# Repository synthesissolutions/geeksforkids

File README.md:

# geeksforkids
car_firmware - Code for RC/Joytick controlled cars

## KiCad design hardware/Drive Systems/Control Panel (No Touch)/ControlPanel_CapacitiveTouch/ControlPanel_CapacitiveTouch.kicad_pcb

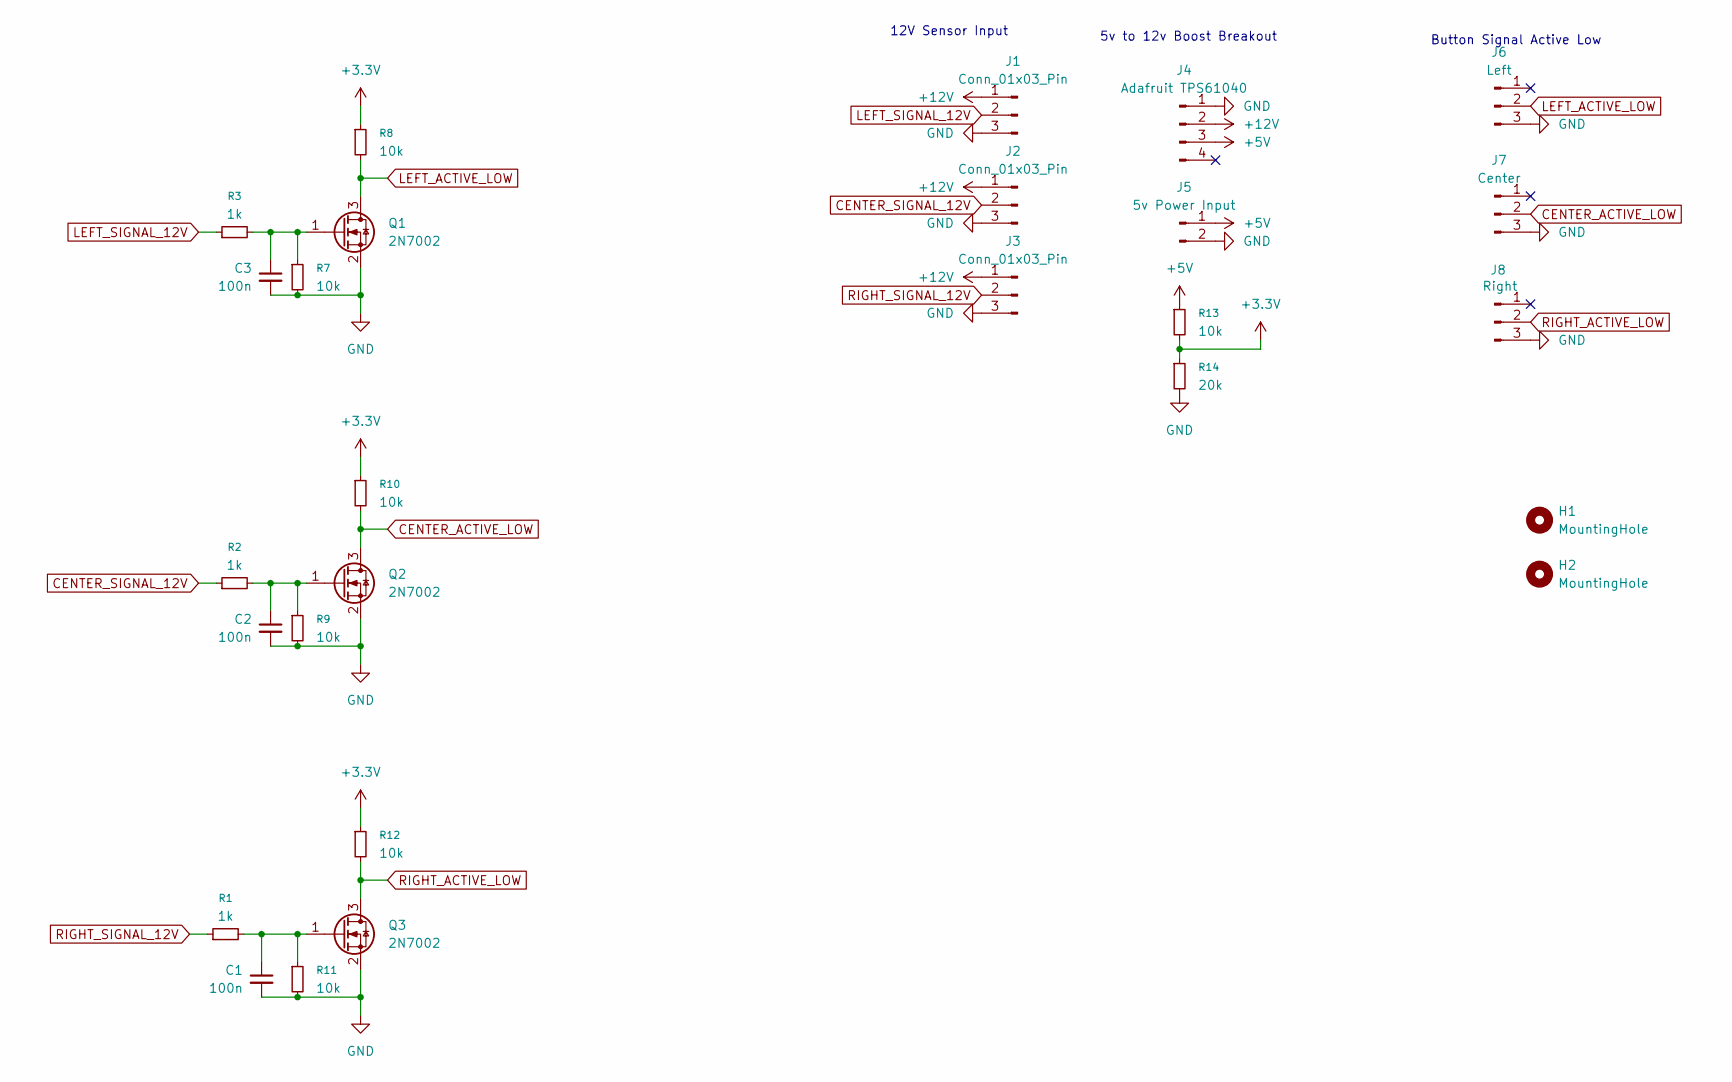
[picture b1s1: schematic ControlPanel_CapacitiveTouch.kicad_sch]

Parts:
C1, C2, C3: 100n; C_0402_1005Metric; MPN C1525
H1, H2: MountingHole; MountingHole_2.7mm_M2.5
J1, J2, J3: Conn_01x03_Pin; JST_PH_B3B-PH-K_1x03_P2.00mm_Vertical
J4: Adafruit TPS61040; PinHeader_1x04_P2.54mm_Vertical
J5: 5v Power Input; JST_XH_B2B-XH-A_1x02_P2.50mm_Vertical
J6: Left; JST_SH_BM03B-SRSS-TB_1x03-1MP_P1.00mm_Vertical; MPN C160403
J7: Center; JST_SH_BM03B-SRSS-TB_1x03-1MP_P1.00mm_Vertical; MPN C160403
J8: Right; JST_SH_BM03B-SRSS-TB_1x03-1MP_P1.00mm_Vertical; MPN C160403
Q1, Q2, Q3: 2N7002; SOT-23; MPN C8545
R1, R2, R3: 1k; R_0402_1005Metric; MPN C11702
R7, R8, R9, R10, R11, R12, R13: 10k; R_0402_1005Metric; MPN C25744
R14: 20k; R_0402_1005Metric; MPN C25765

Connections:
+3.3V: R8.1, R10.1, R12.1, R13.2, R14.1
+5V: J4.3, J5.1, R13.1
+12V: J1.1, J2.1, J3.1, J4.2
CENTER_ACTIVE_LOW: J7.2, Q2.3 (D), R10.2
CENTER_SIGNAL_12V: J2.2, R2.1
GND: C1.2, C2.2, C3.2, J1.3, J2.3, J3.3, J4.1, J5.2, J6.3, J7.3, J8.3, Q1.2 (S), Q2.2 (S), Q3.2 (S), R7.2, R9.2, R11.2, R14.2
LEFT_ACTIVE_LOW: J6.2, Q1.3 (D), R8.2
LEFT_SIGNAL_12V: J1.2, R3.1
unnamed: C3.1, Q1.1 (G), R3.2, R7.1
unnamed: C2.1, Q2.1 (G), R2.2, R9.1
unnamed: C1.1, Q3.1 (G), R1.2, R11.1
RIGHT_ACTIVE_LOW: J8.2, Q3.3 (D), R12.2
RIGHT_SIGNAL_12V: J3.2, R1.1

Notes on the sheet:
5v to 12v Boost Breakout
12V Sensor Input
Button Signal Active Low

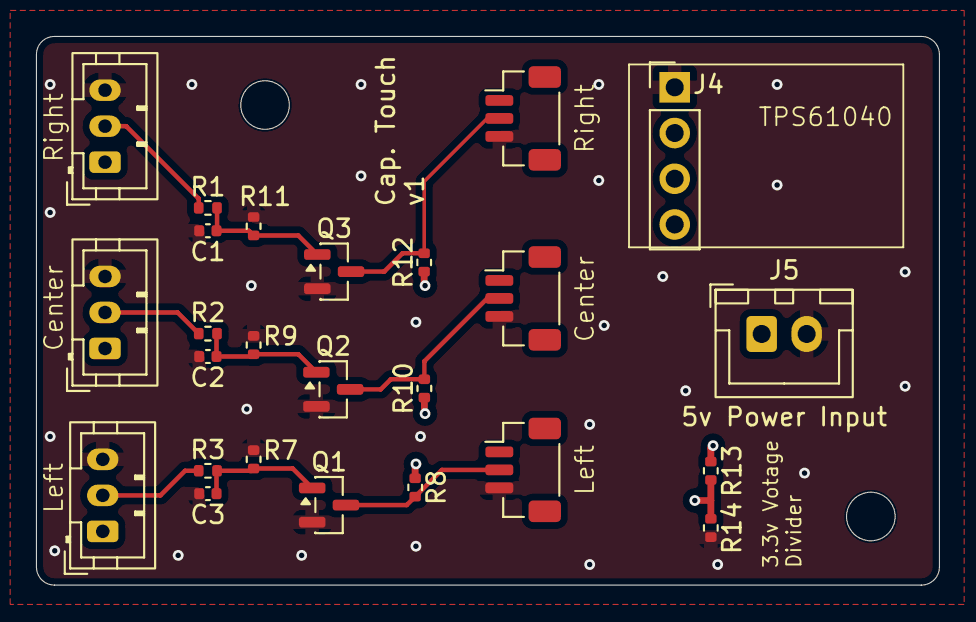
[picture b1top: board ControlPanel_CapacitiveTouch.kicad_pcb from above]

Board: 4 copper layers, 50.2 x 30.5 mm, 27 parts (0 on the bottom side), 13 nets.

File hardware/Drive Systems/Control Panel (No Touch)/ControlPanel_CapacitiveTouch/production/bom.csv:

Designator,Footprint,Quantity,Value,LCSC Part #
"C1, C2, C3",0402,3,100n,C1525
"J1, J2, J3",JST_PH_B3B-PH-K_1x03_P2.00mm_Vertical,3,Conn_01x03_Pin,
J4,PinHeader_1x04_P2.54mm_Vertical,1,Adafruit TPS61040,
J5,JST_XH_B2B-XH-A_1x02_P2.50mm_Vertical,1,5v Power Input,
J6,JST_SH_BM03B-SRSS-TB_1x03-1MP_P1.00mm_Vertical,1,Left,C160403
J7,JST_SH_BM03B-SRSS-TB_1x03-1MP_P1.00mm_Vertical,1,Center,C160403
J8,JST_SH_BM03B-SRSS-TB_1x03-1MP_P1.00mm_Vertical,1,Right,C160403
"Q1, Q2, Q3",SOT-23,3,2N7002,C8545
"R1, R2, R3",0402,3,1k,C11702
"R10, R11, R12, R13, R7, R8, R9",0402,7,10k,C25744
R14,0402,1,20k,C25765

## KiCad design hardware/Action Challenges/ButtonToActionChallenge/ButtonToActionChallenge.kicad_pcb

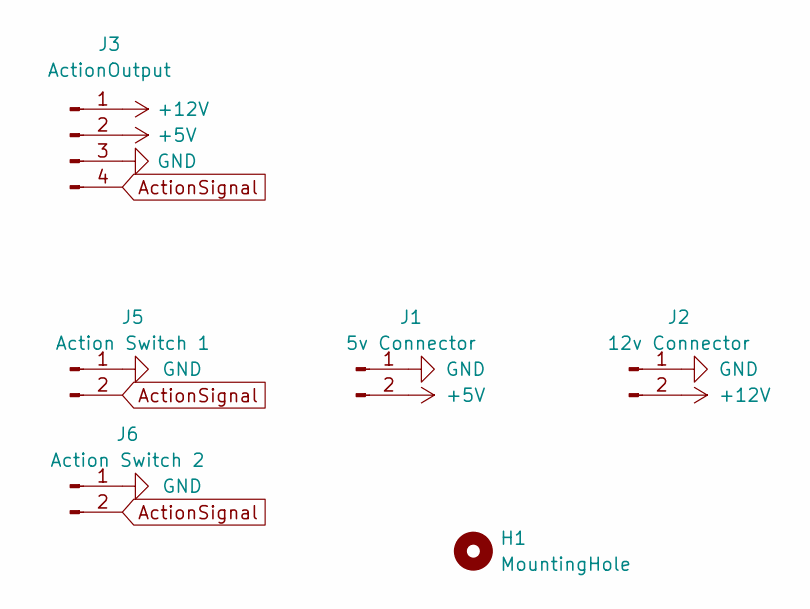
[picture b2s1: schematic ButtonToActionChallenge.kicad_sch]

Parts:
H1: MountingHole; MountingHole_2.7mm_M2.5
J1: 5v Connector; JST_XH_B2B-XH-A_1x02_P2.50mm_Vertical
J2: 12v Connector; JST_XH_B2B-XH-A_1x02_P2.50mm_Vertical
J3: ActionOutput; JST_XH_B4B-XH-A_1x04_P2.50mm_Vertical
J5: Action Switch 1; JST_XH_B2B-XH-A_1x02_P2.50mm_Vertical
J6: Action Switch 2; JST_XH_B2B-XH-A_1x02_P2.50mm_Vertical

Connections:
+5V: J1.2, J3.2
+12V: J2.2, J3.1
ActionSignal: J3.4, J5.2, J6.2
GND: J1.1, J2.1, J3.3, J5.1, J6.1

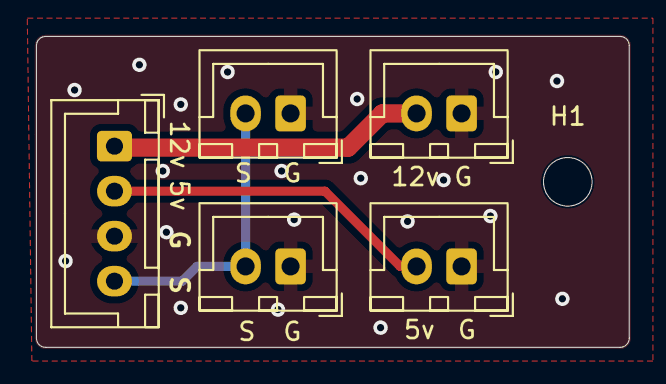
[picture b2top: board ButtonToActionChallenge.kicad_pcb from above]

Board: 2 copper layers, 32.9 x 17.3 mm, 6 parts (0 on the bottom side), 4 nets.

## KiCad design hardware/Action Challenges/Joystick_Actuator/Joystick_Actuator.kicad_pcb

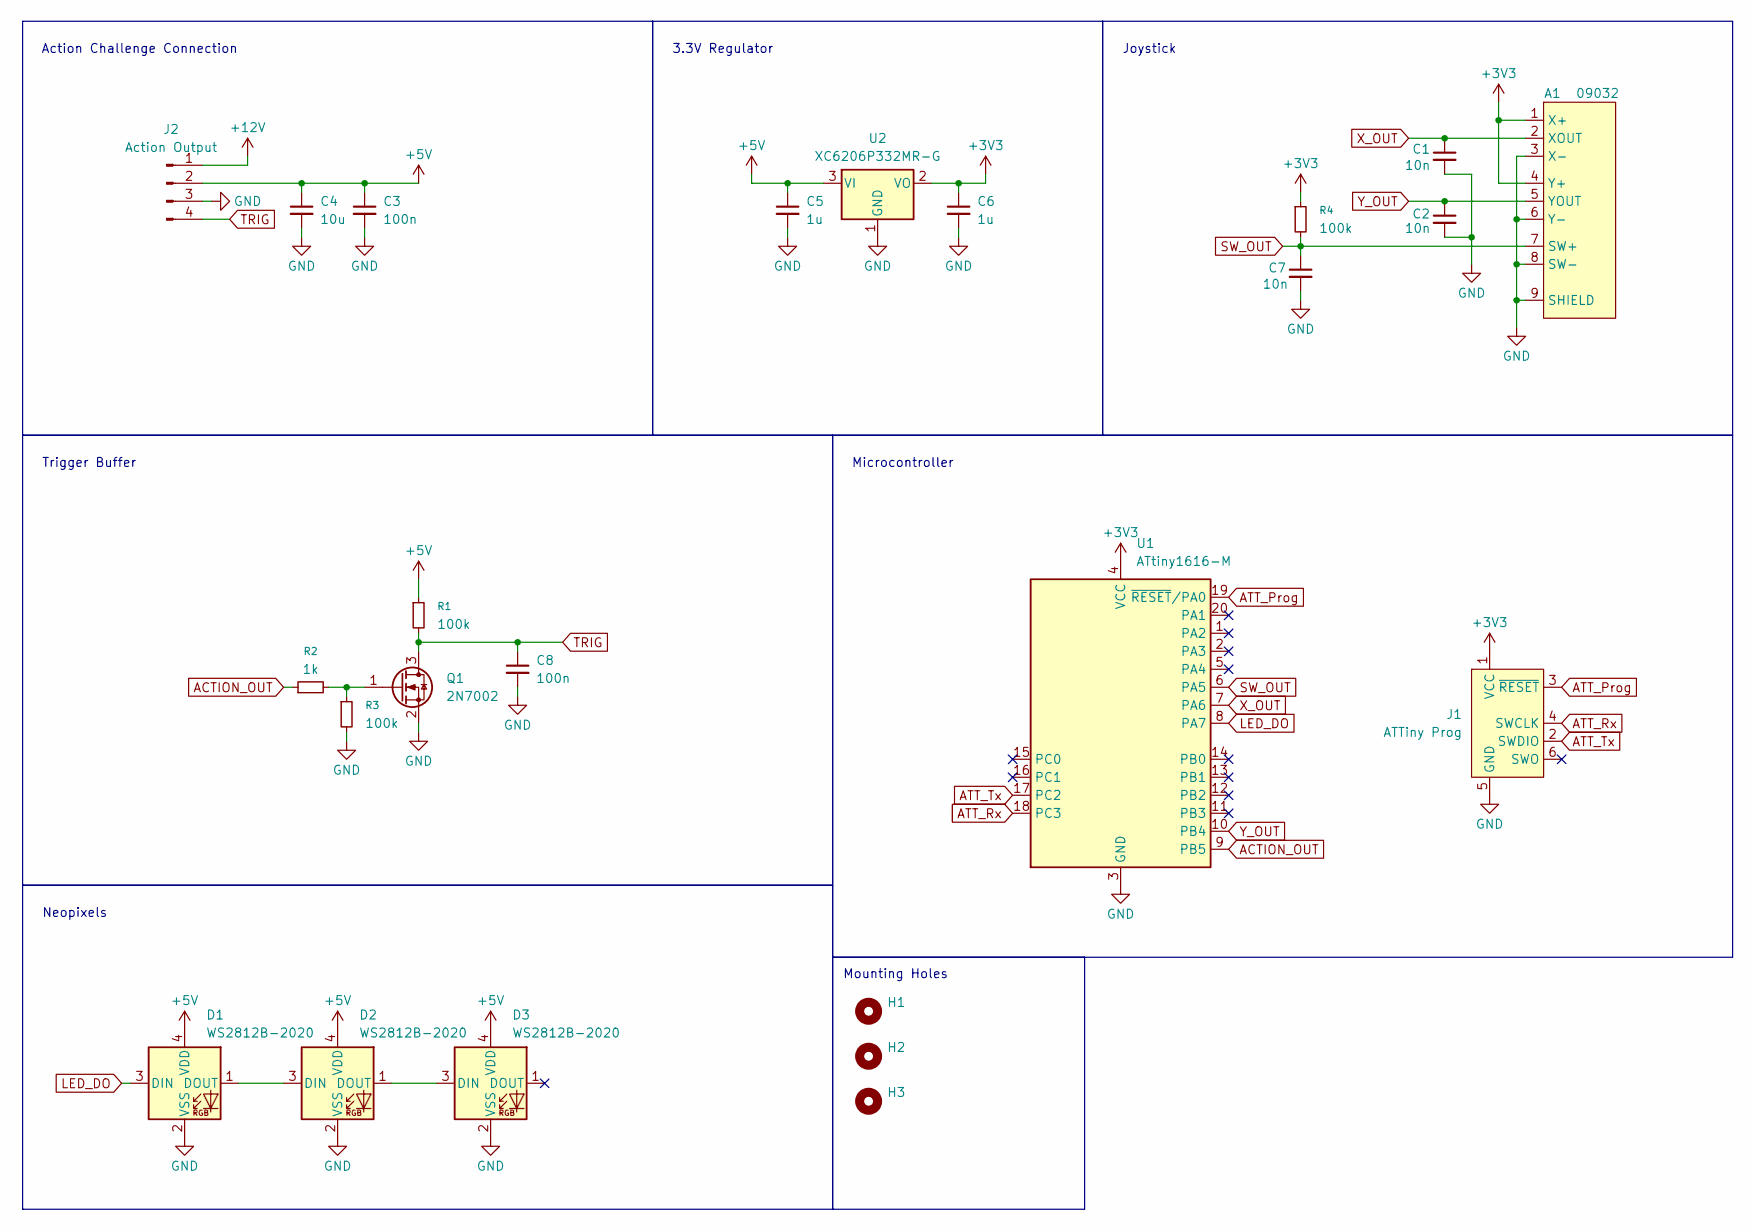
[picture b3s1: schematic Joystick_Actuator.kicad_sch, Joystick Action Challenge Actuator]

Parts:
A1: 09032; Joystick_09032
C1, C2, C7: 10n; C_0402_1005Metric; MPN C15195
C3, C8: 100n; C_0402_1005Metric; MPN C1525
C4: 10u; C_0603_1608Metric; MPN C19702
C5, C6: 1u; C_0402_1005Metric; MPN C52923
D1, D2, D3: WS2812B-2020; LED_WS2812B-2020_PLCC4_2.0x2.0mm; MPN C965555
H1, H2, H3: MountingHole; MountingHole_3.5mm
J1: ATTiny Prog; Tag-Connect_TC2030-IDC-NL_2x03_P1.27mm_Vertical
J2: Action Output; JST_XH_S4B-XH-A_1x04_P2.50mm_Horizontal
Q1: 2N7002; SOT-23; MPN C8545
R1, R3, R4: 100k; R_0402_1005Metric; MPN C25741
R2: 1k; R_0402_1005Metric; MPN C11702
U1: ATtiny1616-M; VQFN-20-1EP_3x3mm_P0.4mm_EP1.7x1.7mm; MPN C507118
U2: XC6206P332MR-G; SOT-23-3; MPN C5446

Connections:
+3V3: A1.1 (X+), A1.4 (Y+), C6.1, J1.1 (VCC), R4.1, U1.4 (VCC), U2.2 (VO)
+5V: C3.1, C4.1, C5.1, D1.4 (VDD), D2.4 (VDD), D3.4 (VDD), J2.2, R1.1, U2.3 (VI)
+12V: J2.1
ACTION_OUT: R2.1, U1.9 (PB5)
ATT_Prog: J1.3 (~RESET), U1.19 (~RESET/PA0)
ATT_Rx: J1.4 (SWCLK), U1.18 (PC3)
ATT_Tx: J1.2 (SWDIO), U1.17 (PC2)
GND: A1.3 (X-), A1.6 (Y-), A1.8 (SW-), A1.9 (SHIELD), C1.2, C2.2, C3.2, C4.2, C5.2, C6.2, C7.2, C8.2, D1.2 (VSS), D2.2 (VSS), D3.2 (VSS), J1.5 (GND), J2.3, Q1.2 (S), R3.2, U1.3 (GND), U1.21 (GND), U2.1 (GND)
LED_DO: D1.3 (DIN), U1.8 (PA7)
unnamed: D1.1 (DOUT), D2.3 (DIN)
unnamed: D2.1 (DOUT), D3.3 (DIN)
unnamed: Q1.1 (G), R2.2, R3.1
SW_OUT: A1.7 (SW+), C7.1, R4.2, U1.6 (PA5)
TRIG: C8.1, J2.4, Q1.3 (D), R1.2
X_OUT: A1.2 (XOUT), C1.1, U1.7 (PA6)
Y_OUT: A1.5 (YOUT), C2.1, U1.10 (PB4)

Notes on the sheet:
Trigger Buffer
Neopixels
Mounting Holes
3.3V Regulator
Microcontroller
Action Challenge Connection
Joystick

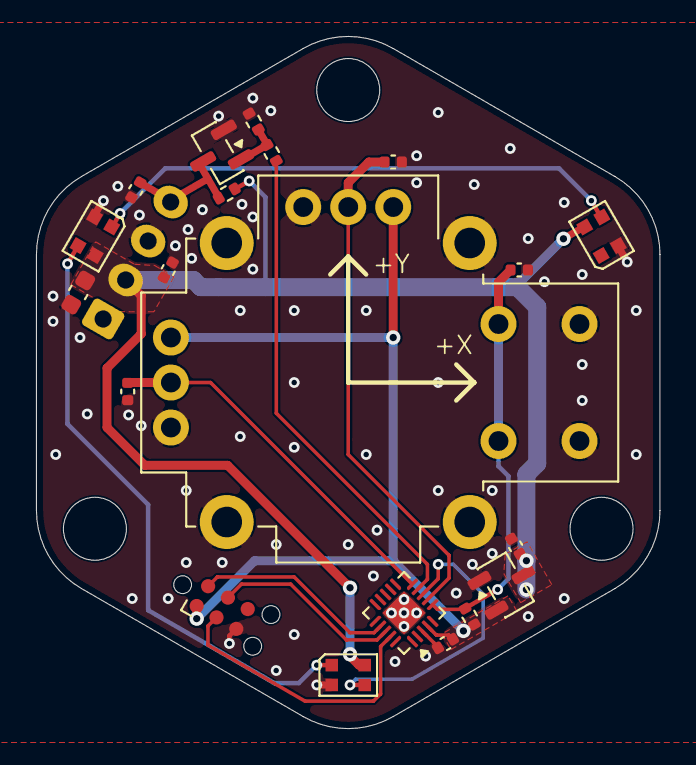
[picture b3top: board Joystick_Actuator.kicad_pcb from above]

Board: 2 copper layers, 34.6 x 38.5 mm, 24 parts (1 on the bottom side), 15 nets.

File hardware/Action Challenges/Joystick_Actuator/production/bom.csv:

Designator,Footprint,Quantity,Value,LCSC Part #
A1,Joystick_09032,1,09032,
"C1, C2, C7",0402,3,10n, C15195
"C3, C8",0402,2,100n,
C4,0603,1,10u,C19702
"C5, C6",0402,2,1u,
"D1, D2, D3",LED_WS2812B-2020_PLCC4_2.0x2.0mm,3,WS2812B-2020,C965555
J2,JST_XH_S4B-XH-A_1x04_P2.50mm_Horizontal,1,Action Output,
Q1,SOT-23,1,2N7002,C8545
"R1, R3, R4",0402,3,100k,C25741
R2,0402,1,1k,C11702
U1,VQFN-20-1EP_3x3mm_P0.4mm_EP1.7x1.7mm,1,ATtiny1616-M,
U2,SOT-23-3,1,XC6206P332MR-G,C5446

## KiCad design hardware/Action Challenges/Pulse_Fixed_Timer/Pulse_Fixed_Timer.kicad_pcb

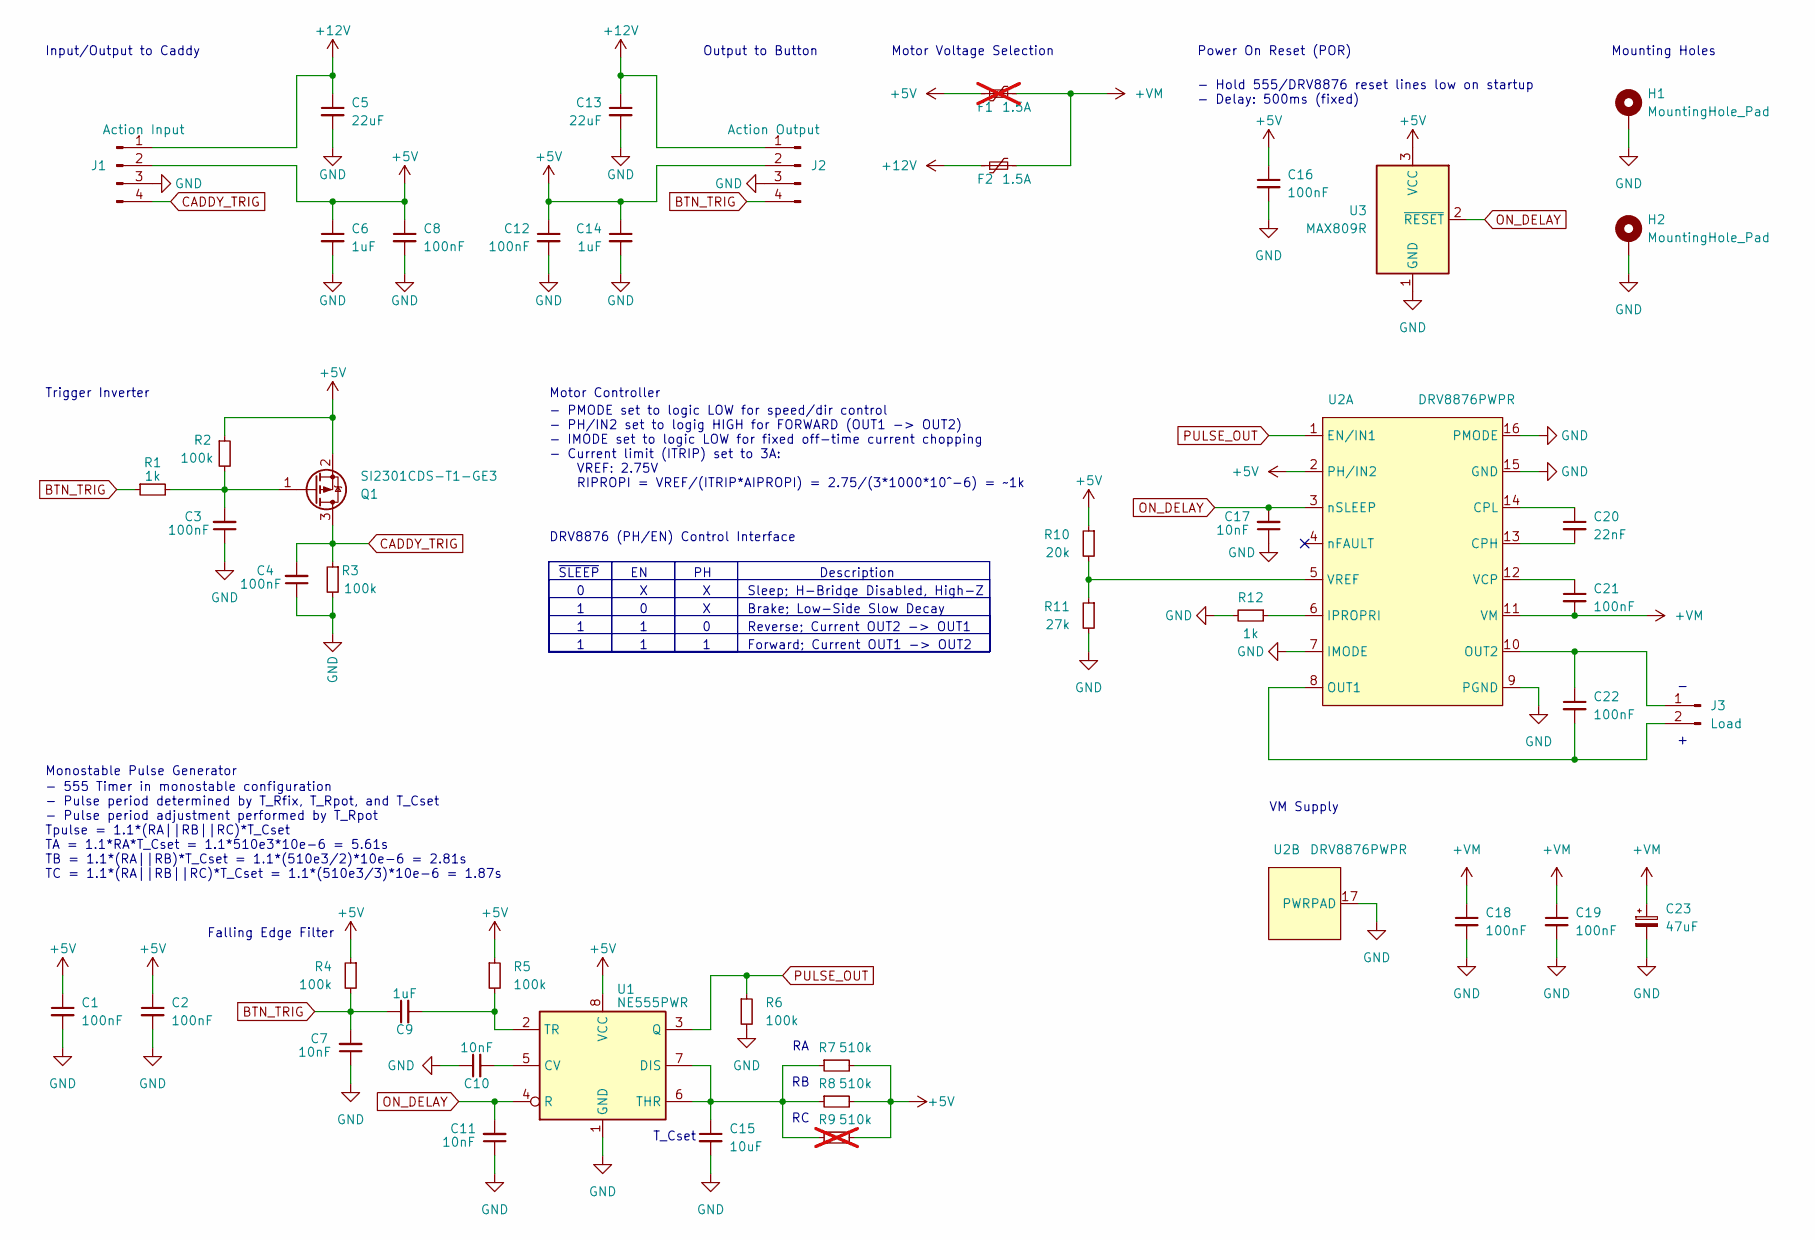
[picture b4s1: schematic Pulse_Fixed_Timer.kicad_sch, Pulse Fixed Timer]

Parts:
C1, C2, C3, C4, C8, C12, C16, C18, C19, C21, C22: 100nF; C_0402_1005Metric; MPN C307331
C5, C13: 22uF; C_0805_2012Metric; MPN C45783
C6, C9, C14: 1uF; C_0402_1005Metric; MPN C52923
C7, C10, C11, C17: 10nF; C_0402_1005Metric; MPN C15195
C15: 10uF; C_0603_1608Metric; MPN C96446
C20: 22nF; C_0402_1005Metric; MPN C1532
C23: 47uF; CP_Elec_6.3x5.4; MPN C3001213
F1: 1.5A; Fuse_1210_3225Metric; MPN C22374902; not fitted
F2: 1.5A; Fuse_1210_3225Metric; MPN C22374902
H1, H2: MountingHole_Pad; MountingHole_2.5mm_Pad
J1: Action Input; JST_XH_B4B-XH-A_1x04_P2.50mm_Vertical
J2: Action Output; JST_XH_B4B-XH-A_1x04_P2.50mm_Vertical
J3: Load; JST_XH_B2B-XH-A_1x02_P2.50mm_Vertical
Q1: SI2301CDS-T1-GE3; SOT-23; MPN C10487
R1, R12: 1k; R_0402_1005Metric; MPN C11702
R2, R3, R4, R5, R6: 100k; R_0402_1005Metric; MPN C25741
R7, R8: 510k; R_0603_1608Metric; MPN C23192
R9: 510k; R_0603_1608Metric; MPN C23192; not fitted
R10: 20k; R_0402_1005Metric; MPN C25765
R11: 27k; R_0402_1005Metric; MPN C25771
U1: NE555PWR; TSSOP-8_4.4x3mm_P0.65mm; MPN C105643
U2: DRV8876PWPR; HTSSOP-16-1EP_4.4x5mm_P0.65mm_EP3.4x5mm_Mask2.46x2.31mm; MPN C575551
U3: MAX809R; SOT-23; MPN C19631717

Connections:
+5V: C1.1, C2.1, C6.1, C8.1, C12.1, C14.1, C16.1, F1.1, J1.2, J2.2, Q1.2 (S), R2.1, R4.1, R5.1, R7.2, R8.2, R9.2, R10.1, U1.8 (VCC), U2.2 (PH/IN2), U3.3 (VCC)
+12V: C5.1, C13.1, F2.1, J1.1, J2.1
+VM: C18.1, C19.1, C21.2, C23.1, F1.2, F2.2, U2.11 (VM)
BTN_TRIG: C7.2, C9.1, J2.4, R1.1, R4.2
CADDY_TRIG: C4.2, J1.4, Q1.3 (D), R3.1
GND: C1.2, C2.2, C3.1, C4.1, C5.2, C6.2, C7.1, C8.2, C10.1, C11.1, C12.2, C13.2, C14.2, C15.2, C16.2, C17.1, C18.2, C19.2, C23.2, H1.1, H2.1, J1.3, J2.3, R3.2, R6.2, R11.2, R12.2, U1.1 (GND), U2.7 (IMODE), U2.9 (PGND), U2.15 (GND), U2.16 (PMODE), U2.17 (PWRPAD), U3.1 (GND)
unnamed: C22.1, J3.1, U2.10 (OUT2)
unnamed: C22.2, J3.2, U2.8 (OUT1)
unnamed: C3.2, Q1.1 (G), R1.2, R2.2
unnamed: C10.2, U1.5 (CV)
unnamed: C15.1, R7.1, R8.1, R9.1, U1.6 (THR), U1.7 (DIS)
unnamed: C9.2, R5.2, U1.2 (TR)
unnamed: C20.2, U2.13 (CPH)
unnamed: C20.1, U2.14 (CPL)
unnamed: R12.1, U2.6 (IPROPRI)
unnamed: C21.1, U2.12 (VCP)
unnamed: R10.2, R11.1, U2.5 (VREF)
ON_DELAY: C11.2, C17.2, U1.4 (R), U2.3 (nSLEEP), U3.2 (~RESET)
PULSE_OUT: R6.1, U1.3 (Q), U2.1 (EN/IN1)

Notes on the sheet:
Description
- 555 Timer in monostable configuration - Pulse period determined by T_Rfix, T_Rpot, and T_Cset - Pulse period adjustment performed by T_Rpot Tpulse = 1.1*(RA||RB||RC)*T_Cset TA = 1.1*RA*T_Cset = 1.1*510e3*10e-6 = 5.61s TB = 1.1*(RA||RB)*T_Cset = 1.1*(510e3/2)*10e-6 = 2.81s TC = 1.1*(RA||RB||RC)*T_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
Brake; Low-Side Slow Decay
Monostable Pulse Generator
Trigger Inverter
Reverse; Current OUT2 -> OUT1
- PMODE set to logic LOW for speed/dir control - PH/IN2 set to logig HIGH for FORWARD (OUT1 -> OUT2) - IMODE set to logic LOW for fixed off-time current chopping - Current limit (ITRIP) set to 3A: VREF: 2.75V RIPROPI = VREF/(ITRIP*AIPROPI) = 2.75/(3*1000*10^-6) = ~1k
DRV8876 (PH/EN) Control Interface
Motor Voltage Selection
~{SLEEP}
Forward; Current OUT1 -> OUT2
Falling Edge Filter
- Hold 555/DRV8876 reset lines low on startup - Delay: 500ms (fixed)
Mounting Holes
VM Supply
Motor Controller
Output to Button
T_Cset
Sleep; H-Bridge Disabled, High-Z
Power On Reset (POR)
Input/Output to Caddy

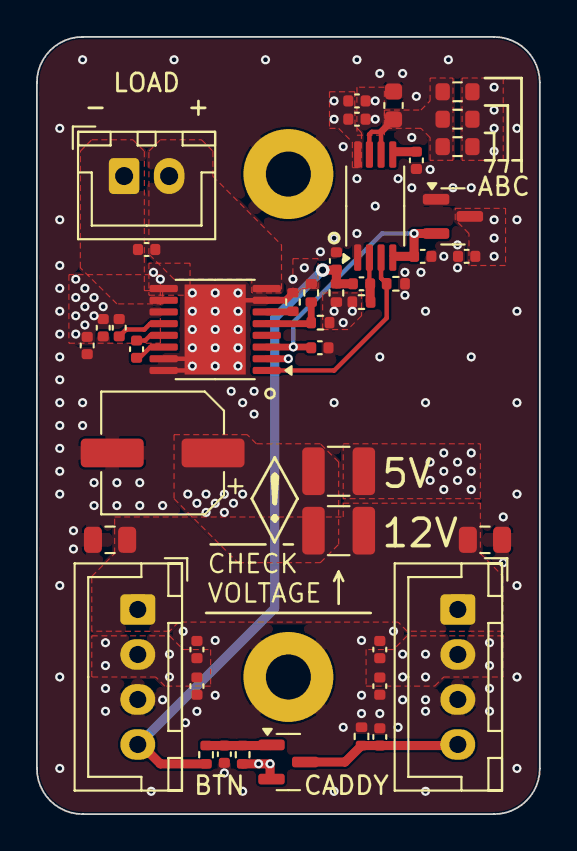
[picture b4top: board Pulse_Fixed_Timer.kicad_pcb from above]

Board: 4 copper layers, 27.9 x 43.2 mm, 46 parts (0 on the bottom side), 19 nets.

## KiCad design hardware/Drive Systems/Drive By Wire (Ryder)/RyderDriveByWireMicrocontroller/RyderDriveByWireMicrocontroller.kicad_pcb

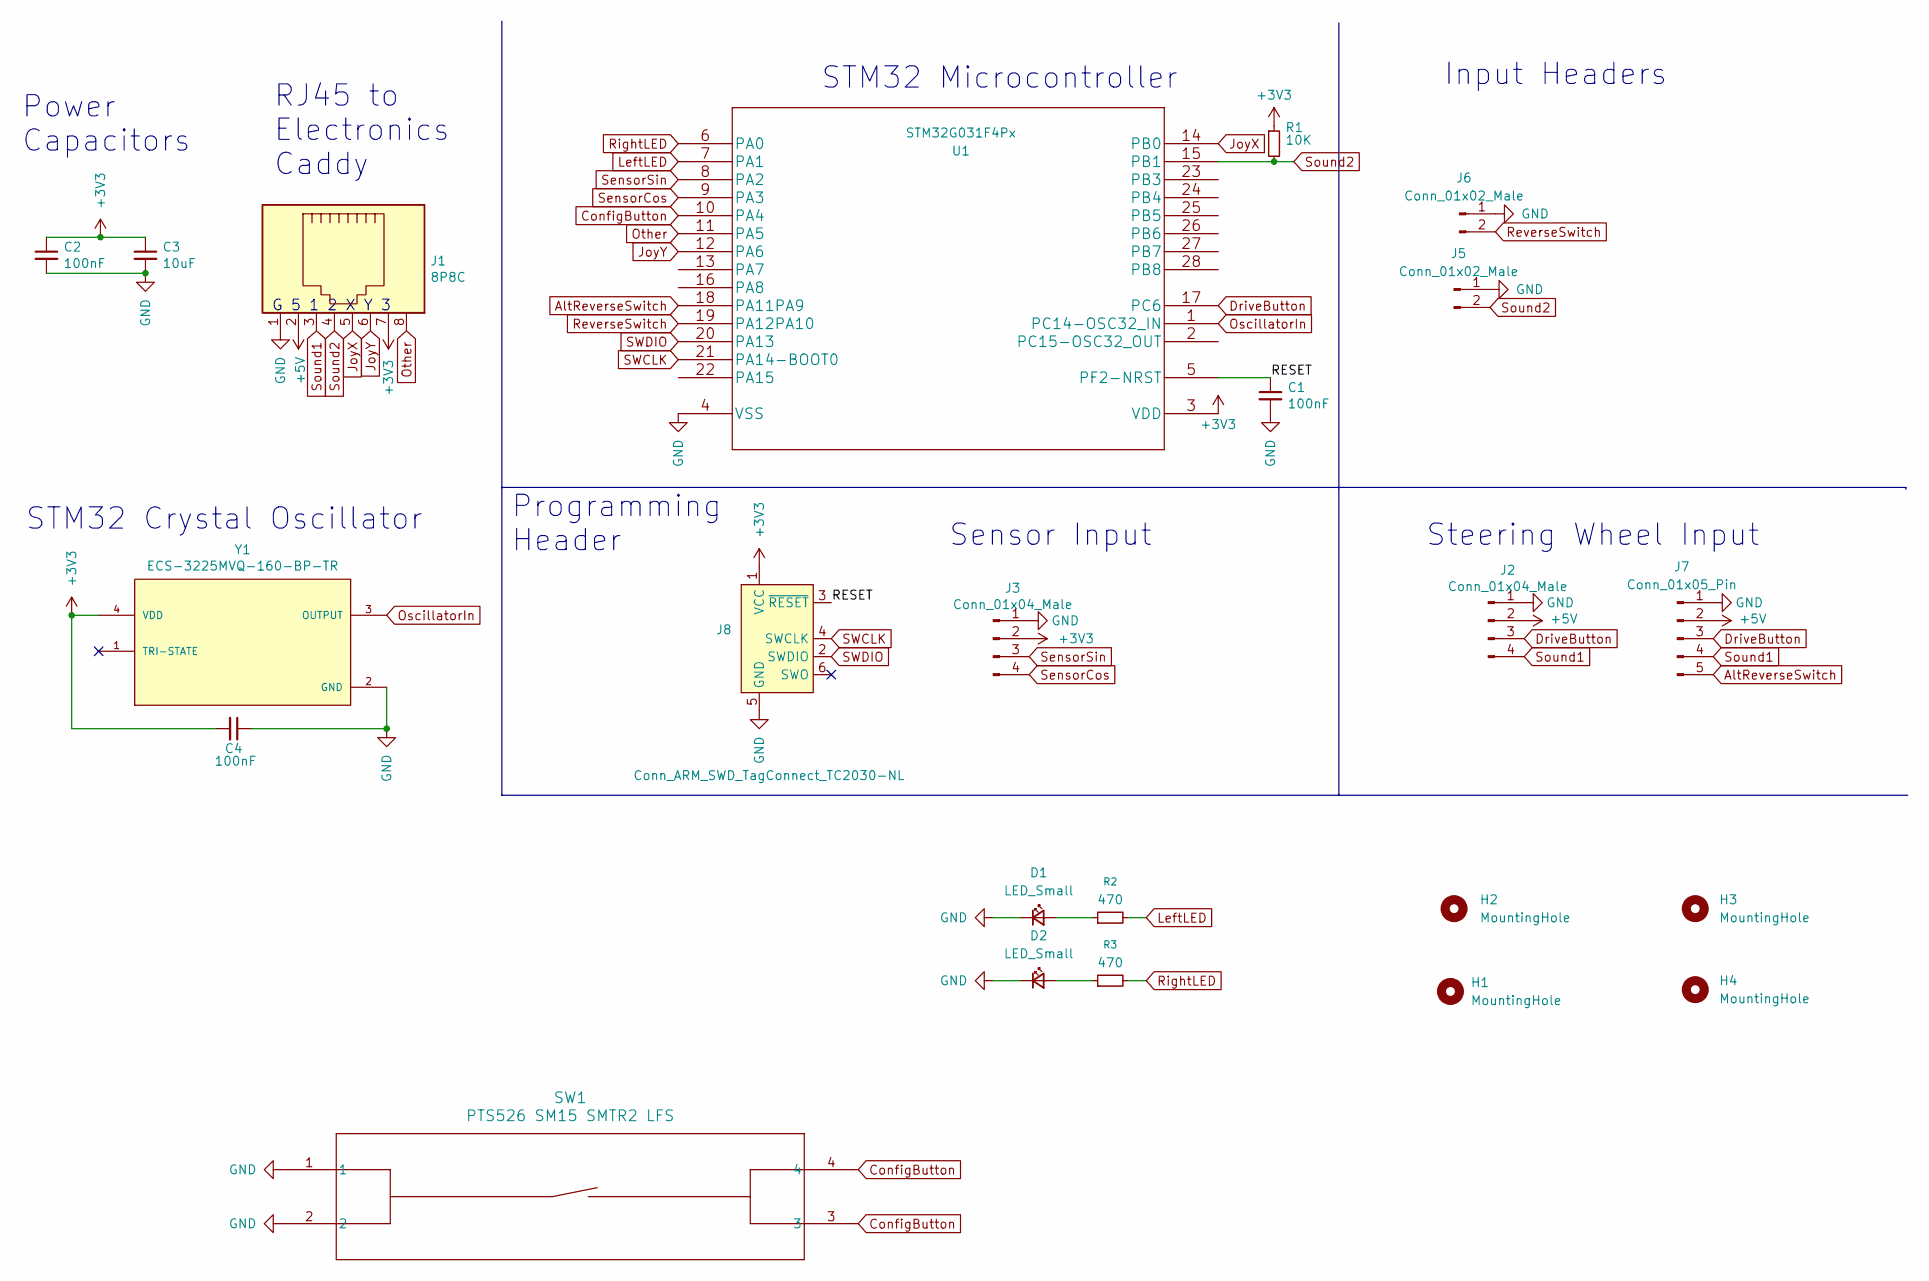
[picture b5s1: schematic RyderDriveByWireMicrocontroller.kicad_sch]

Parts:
C1, C2, C4: 100nF; C_0402_1005Metric; MPN C307331
C3: 10uF; C_0402_1005Metric; MPN C315248
D1, D2: LED_Small; LED_0603_1608Metric; MPN C965799
H1, H2, H3, H4: MountingHole; MountingHole_2.7mm_M2.5
J1: 8P8C; RJHSE3085a
J2, J3: Conn_01x04_Male; JST_SH_BM04B-SRSS-TB_1x04-1MP_P1.00mm_Vertical; MPN C145961
J5, J6: Conn_01x02_Male; JST_XH_B2B-XH-A_1x02_P2.50mm_Vertical
J7: Conn_01x05_Pin; JST_SH_BM05B-SRSS-TB_1x05-1MP_P1.00mm_Vertical; MPN C2845373
J8: Conn_ARM_SWD_TagConnect_TC2030-NL; Tag-Connect_TC2030-IDC-NL_2x03_P1.27mm_Vertical
R1: 10K; R_0402_1005Metric; MPN C2906861
R2, R3: 470; R_0402_1005Metric; MPN C2909361
SW1: PTS526 SM15 SMTR2 LFS; SON4_PTS526 SM15 SMTR2 LFS_CNK
U1: STM32G031F4Px; STM32G031G8U6; MPN C432211
Y1: ECS-3225MVQ-160-BP-TR; OSC_ECS-3225MVQ-160-BP-TR; MPN C252336

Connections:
+3V3: C2.1, C3.1, C4.2, J1.7, J3.2, J8.1 (VCC), R1.1, U1.3 (VDD), Y1.4 (VDD)
+5V: J1.2, J2.2, J7.2
/RESET: C1.1, J8.3 (~RESET), U1.5 (PF2-NRST)
AltReverseSwitch: J7.5, U1.18 (PA11PA9)
ConfigButton: SW1.3, SW1.4, U1.10 (PA4)
DriveButton: J2.3, J7.3, U1.17 (PC6)
GND: C1.2, C2.2, C3.2, C4.1, D1.1 (K), D2.1 (K), J1.1, J2.1, J3.1, J5.1, J6.1, J7.1, J8.5 (GND), SW1.1, SW1.2, U1.4 (VSS), Y1.2 (GND)
JoyX: J1.5, U1.14 (PB0)
JoyY: J1.6, U1.12 (PA6)
LeftLED: R2.2, U1.7 (PA1)
unnamed: D1.2 (A), R2.1
unnamed: D2.2 (A), R3.1
OscillatorIn: U1.1 (PC14-OSC32_IN), Y1.3 (OUTPUT)
Other: J1.8, U1.11 (PA5)
ReverseSwitch: J6.2, U1.19 (PA12PA10)
RightLED: R3.2, U1.6 (PA0)
SWCLK: J8.4 (SWCLK), U1.21 (PA14-BOOT0)
SWDIO: J8.2 (SWDIO), U1.20 (PA13)
SensorCos: J3.4, U1.9 (PA3)
SensorSin: J3.3, U1.8 (PA2)
Sound1: J1.3, J2.4, J7.4
Sound2: J1.4, J5.2, R1.2, U1.15 (PB1)

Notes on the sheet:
Steering Wheel Input
Programming Header
Input Headers
Power Capacitors
STM32 Microcontroller
Sensor Input
RJ45 to Electronics Caddy
G 5 1 2 X Y 3
STM32 Crystal Oscillator

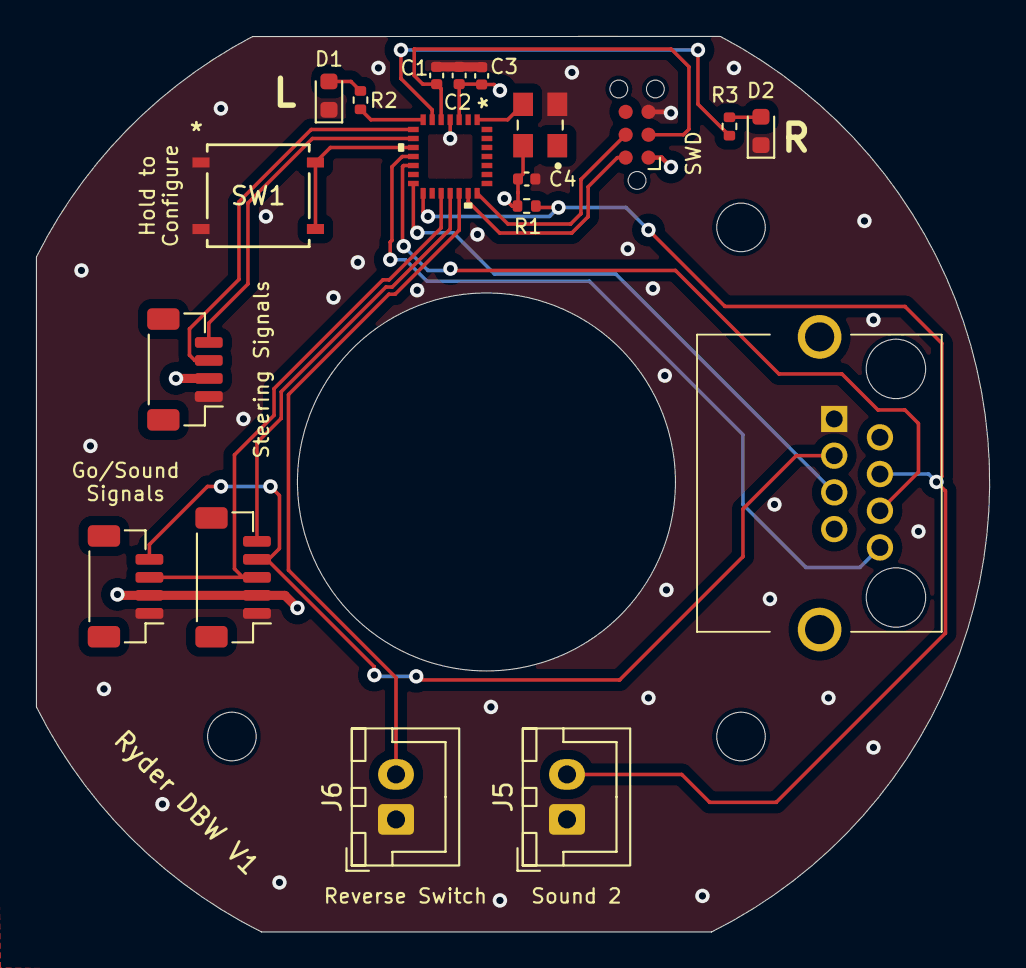
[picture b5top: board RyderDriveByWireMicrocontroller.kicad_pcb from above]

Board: 4 copper layers, 53.0 x 49.8 mm, 22 parts (0 on the bottom side), 22 nets.

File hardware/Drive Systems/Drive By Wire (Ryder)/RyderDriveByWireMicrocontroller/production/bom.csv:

Designator,Footprint,Quantity,Value,LCSC Part #
"C1, C2, C4",0402,3,100nF,C307331
C3,0402,1,10uF,C315248
"D1, D2",0603,2,LED_Small,C965799
"H1, H3, H4",MountingHole_2.7mm_M2.5,3,MountingHole,
J1,RJHSE3085a,1,8P8C,
"J2, J3",JST_SH_BM04B-SRSS-TB_1x04-1MP_P1.00mm_Vertical,2,Conn_01x04_Male,C7433440
"J5, J6",JST_XH_B2B-XH-A_1x02_P2.50mm_Vertical,2,Conn_01x02_Male,
J7,JST_SH_BM05B-SRSS-TB_1x05-1MP_P1.00mm_Vertical,1,Conn_01x05_Pin,C2845373
R1,0402,1,10K,C2906861
"R2, R3",0402,2,470,C2909361
SW1,SON4_PTS526 SM15 SMTR2 LFS_CNK,1,PTS526 SM15 SMTR2 LFS,C49234134
U1,STM32G031G8U6,1,STM32G031F4Px,C432211
Y1,OSC_ECS-3225MVQ-160-BP-TR,1,ECS-3225MVQ-160-BP-TR,C252336

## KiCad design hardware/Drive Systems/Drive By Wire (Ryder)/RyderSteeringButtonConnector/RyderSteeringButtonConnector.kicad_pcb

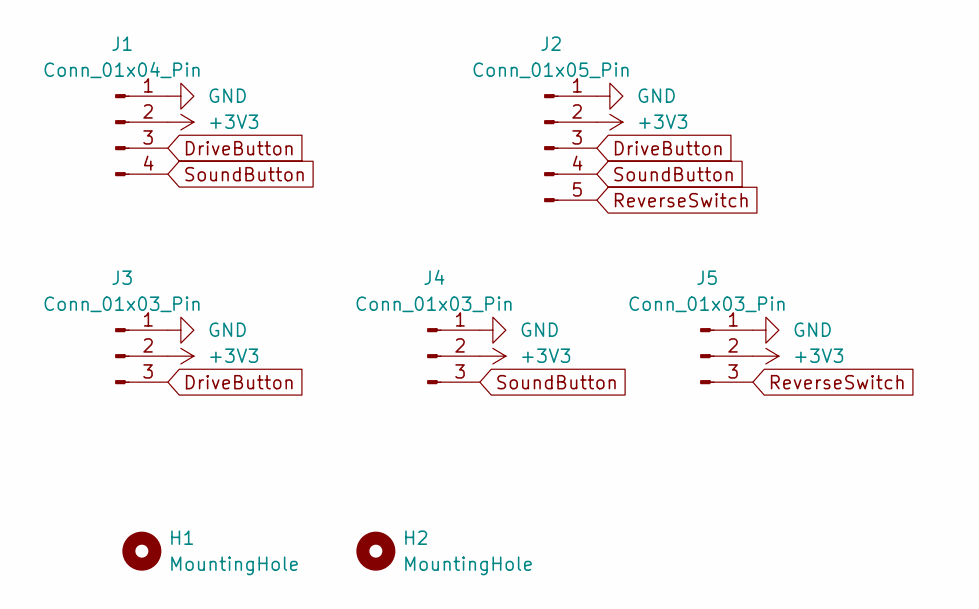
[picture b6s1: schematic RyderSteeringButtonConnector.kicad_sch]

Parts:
H1, H2: MountingHole; MountingHole_2.7mm_M2.5
J1: Conn_01x04_Pin; JST_SH_SM04B-SRSS-TB_1x04-1MP_P1.00mm_Horizontal; LCSC Part # C160404
J2: Conn_01x05_Pin; JST_SH_SM05B-SRSS-TB_1x05-1MP_P1.00mm_Horizontal; LCSC Part # C136657
J3, J4, J5: Conn_01x03_Pin; JST_SH_BM03B-SRSS-TB_1x03-1MP_P1.00mm_Vertical; LCSC Part # C160389

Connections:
+3V3: J1.2, J2.2, J3.2, J4.2, J5.2
DriveButton: J1.3, J2.3, J3.3
GND: J1.1, J2.1, J3.1, J4.1, J5.1
ReverseSwitch: J2.5, J5.3
SoundButton: J1.4, J2.4, J4.3

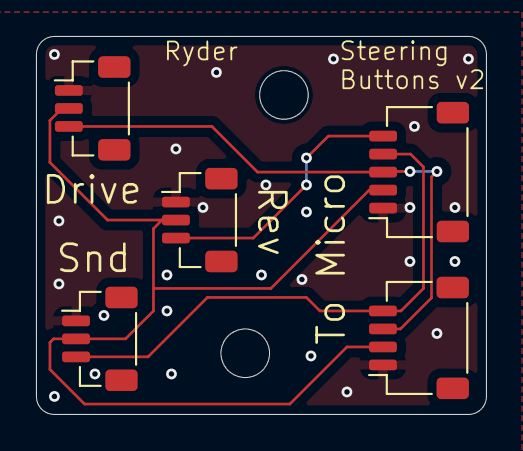
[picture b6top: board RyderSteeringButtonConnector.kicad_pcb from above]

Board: 2 copper layers, 25.0 x 21.0 mm, 7 parts (0 on the bottom side), 5 nets.

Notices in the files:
parts and their libraries:
Copyright 2021 Accelerated Designs. All rights reserved.
